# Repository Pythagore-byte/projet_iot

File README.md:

# projet_iot

## Project Overview

This repository contains an IoT project involving sensor data collection, backend processing, and a frontend dashboard. It encompasses Arduino firmware for sensor interfacing, a Python-based backend for data management and MQTT communication, a KiCad design for custom hardware, and a TypeScript/Next.js frontend for data visualization and user interaction.

## Key Features & Benefits

- **Multi-Sensor Integration:** Supports various sensors including temperature, humidity, soil moisture, CO2, and light.
- **LoRaWAN Connectivity:** Utilizes LoRaWAN for long-range, low-power data transmission.
- **Data Processing & Storage:** Employs a Python backend with SQLite database for data ingestion, processing, and storage.
- **Real-time Data Visualization:** Provides a user-friendly dashboard built with Next.js to monitor sensor data in real-time.
- **Custom Hardware Design:** Includes KiCad files for building custom PCB hardware.
- **Containerized Deployment:** Docker support for backend and frontend simplifies deployment and ensures consistency.

## Prerequisites & Dependencies

Before you begin, ensure you have the following installed:

- **Arduino IDE:** For flashing the Arduino firmware.
- **Python 3.11:** For running the backend server and related scripts.
- **Node.js and npm:** For building and running the frontend application.
- **Docker and Docker Compose:** For containerized deployment.
- **KiCad:** For viewing and editing the hardware design files.

**Specific Python Dependencies (Backend):**

- `fastapi`
- `uvicorn`
- `paho-mqtt`
- `sqlite3`
- `python-dotenv`

Install them using:

```bash
pip install -r backend/requirements.txt
```

**Specific Node.js Dependencies (Frontend):**

Refer to `frontend/package.json` for a complete list.  Install them using:

```bash
cd frontend
npm install
```

## Installation & Setup Instructions

Follow these steps to set up and run the project:

1. **Clone the Repository:**

   ```bash
   git clone https://github.com/Pythagore-byte/projet_iot.git
   cd projet_iot
   ```

2. **Arduino Firmware (Arduino_TTN):**

   - Open `Arduino_TTN/Arduino_TTN.ino` in the Arduino IDE.
   - Configure the necessary libraries and board settings for your specific hardware.
   - Modify the LoRaWAN credentials and sensor configurations as needed.
   - Upload the firmware to your Arduino device.

3. **Backend Setup:**

   - Navigate to the `backend` directory:

     ```bash
     cd backend
     ```

   -  Set up environment variables if needed (e.g., for production). Consider using `.env` file and `python-dotenv`.

   -  Initialize the database (if not already present):
      - Development Database:
        ```bash
        python dev_db_generator.py
        ```
      - Production Database:
        ```bash
        python prod_db_generator.py
        ```
      - Or use the provided `db.db` file.

   - Run the backend server:

     ```bash
     python server.py
     ```

     Alternatively, for Docker deployment, see step 5.

4. **Frontend Setup:**

   - Navigate to the `frontend` directory:

     ```bash
     cd ../frontend
     ```

   - Install the dependencies:

     ```bash
     npm install
     ```

   - Configure API endpoint in `frontend/lib/api.ts` to point to your backend server.

   - Run the development server:

     ```bash
     npm run dev
     ```

     This will start the frontend application, typically on `http://localhost:3000`.

5. **Docker Compose Deployment:**

   - From the project root directory, run:

     ```bash
     docker-compose up --build
     ```

   - This will build and start both the backend and frontend containers. Access the frontend through the port defined in the `docker-compose.yml` file (usually `http://localhost:3000`).

6. **KiCad Files (KICAD_FILES):**

   - Open the `.kicad_pcb` and `.kicad_sch` files in KiCad to view and modify the hardware design.

## Usage Examples & API Documentation

### Backend API (Example):

The backend provides a REST API for accessing sensor data.  Example endpoints:

- `GET /data`: Returns all sensor data.
- `GET /data/{device_id}`: Returns data for a specific device ID.

Refer to `backend/server.py` for detailed API route definitions.

### Frontend Usage:

The frontend provides a user interface for visualizing sensor data. Navigate to the appropriate page in your browser to see the collected data and related analysis. The routes `/soil-data`, `/temperature-humidity` and `/plant-suitability` will show the corresponding information.

## Configuration Options

### Backend Configuration:

- **Database Path:** The path to the SQLite database can be configured in `backend/server.py`.
- **MQTT Configuration:** The MQTT broker address, port, app ID, device ID and access key can be configured in `backend/mqtt_adder.py`.
- **Port:** The backend server port can be configured via the `--port` flag when starting the server (e.g., `uvicorn server:app --host 0.0.0.0 --port 8000`).

### Frontend Configuration:

- **API Endpoint:** The backend API endpoint URL should be defined in `frontend/lib/api.ts`.
- **Environment Variables:** Use environment variables in `next.config.js` to configure aspects of frontend deployment.

## Contributing Guidelines

We welcome contributions to this project! To contribute:

1. Fork the repository.
2. Create a new branch for your feature or bug fix.
3. Implement your changes.
4. Submit a pull request with a clear description of your changes.
5. Ensure code follows style conventions and has proper documentation.

## License Information

This project has no specific license specified. All rights are reserved by the owner.

## Acknowledgments

- This project utilizes open-source libraries and tools. We thank the developers and maintainers of these resources.

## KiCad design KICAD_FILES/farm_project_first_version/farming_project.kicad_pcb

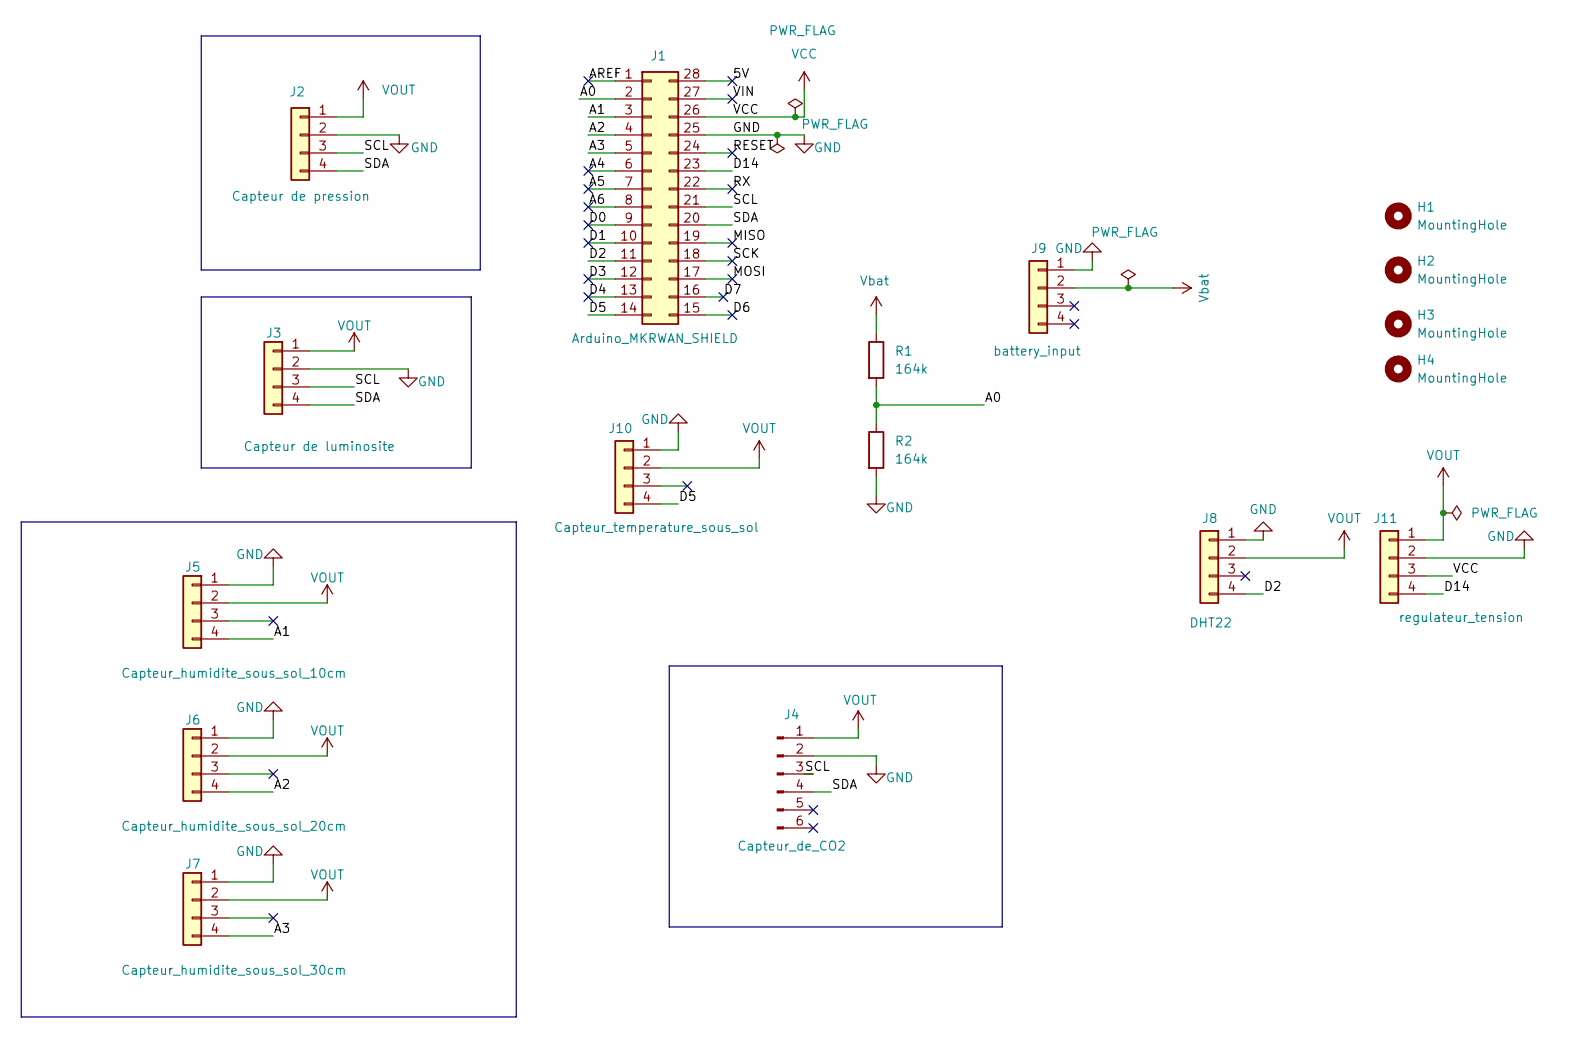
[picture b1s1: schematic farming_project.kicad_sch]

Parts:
H1, H2, H3, H4: MountingHole; MountingHole_2.5mm_Pad
J1: Arduino_MKRWAN_SHIELD; BOARD_ARDUINO_MKR_WAN_1310_MODIFIED
J2: Capteur de pression; PinSocket_1x04_P2.54mm_Vertical
J3: Capteur de luminosite; PinHeader_1x04_P2.54mm_Vertical
J4: Capteur_de_CO2; PinSocket_1x06_P2.54mm_Vertical
J5: Capteur_humidite_sous_sol_10cm; JST_PH_B4B-PH-K_1x04_P2.00mm_Vertical
J6: Capteur_humidite_sous_sol_20cm; JST_PH_B4B-PH-K_1x04_P2.00mm_Vertical
J7: Capteur_humidite_sous_sol_30cm; JST_PH_B4B-PH-K_1x04_P2.00mm_Vertical
J8: DHT22; JST_PH_B4B-PH-K_1x04_P2.00mm_Vertical
J9: battery_input; JST_PH_B4B-PH-K_1x04_P2.00mm_Vertical
J10: Capteur_temperature_sous_sol; JST_PH_B4B-PH-K_1x04_P2.00mm_Vertical
J11: regulateur_tension; PinHeader_1x04_P2.54mm_Vertical
R1, R2: 164k; R_Axial_DIN0309_L9.0mm_D3.2mm_P12.70mm_Horizontal

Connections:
/5V: J1.28
/A0: J1.2, R1.2, R2.1
/A1: J1.3, J5.4
/A2: J1.4, J6.4
/A3: J1.5, J7.4
/A4: J1.6
/A5: J1.7
/A6: J1.8
/AREF: J1.1
/D0: J1.9
/D1: J1.10
/D2: J1.11, J8.4
/D3: J1.12
/D4: J1.13
/D5: J1.14, J10.4
/D6: J1.15
/D7: J1.16
/D14: J1.23, J11.4
/MISO: J1.19
/MOSI: J1.17
/RESET: J1.24
/RX: J1.22
/SCK: J1.18
/SCL: J1.21, J2.3, J3.3, J4.3
/SDA: J1.20, J2.4, J3.4, J4.4
/VIN: J1.27
GND: J1.25, J2.2, J3.2, J4.2, J5.1, J6.1, J7.1, J8.1, J9.1, J10.1, J11.2, R2.2
VCC: J1.26, J11.3
VOUT: J2.1, J3.1, J4.1, J5.2, J6.2, J7.2, J8.2, J10.2, J11.1
Vbat: J9.2, R1.1

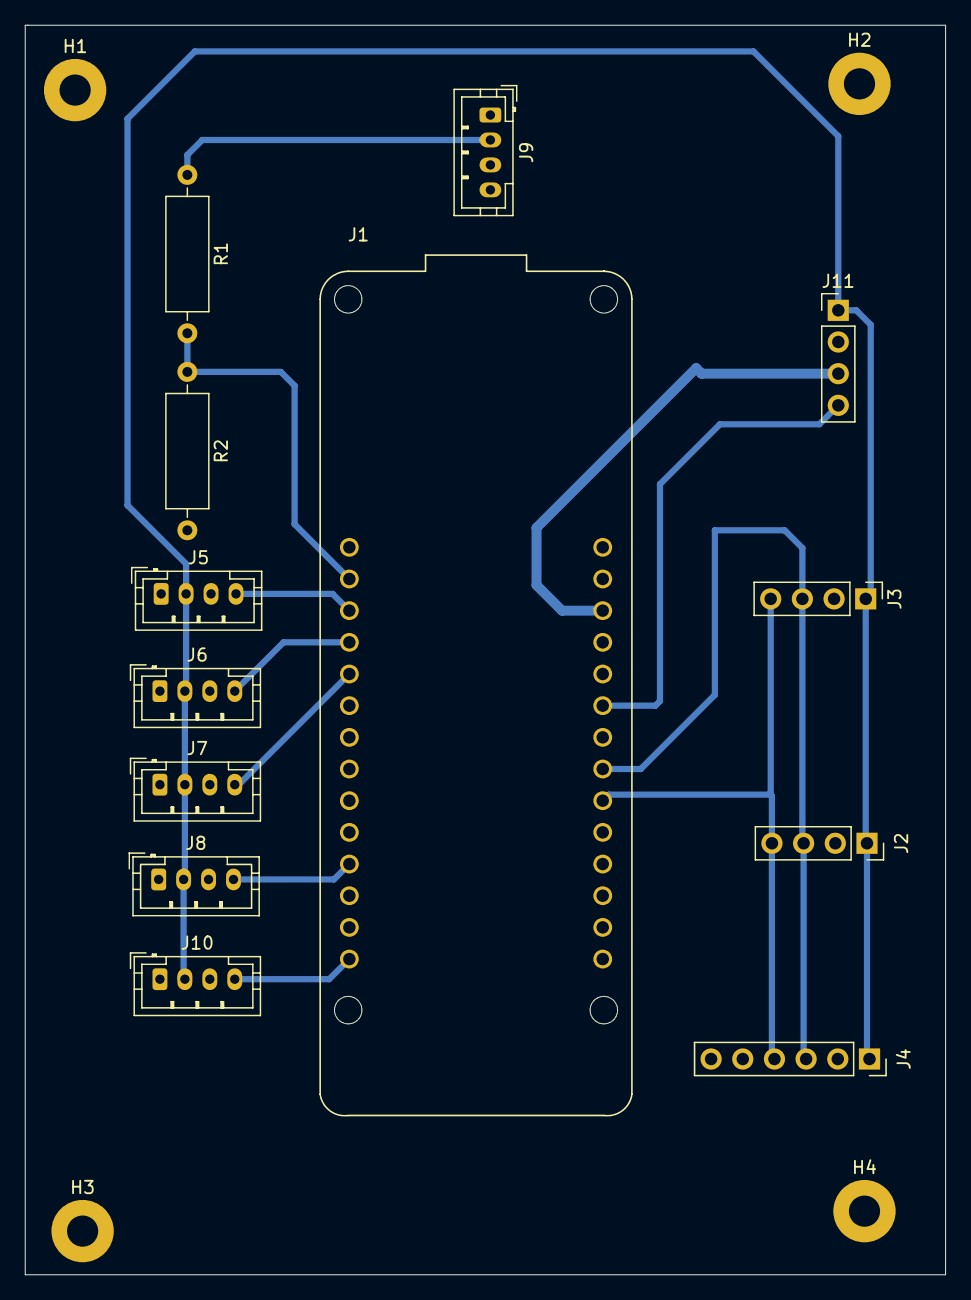
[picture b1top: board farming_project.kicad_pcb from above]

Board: 2 copper layers, 73.8 x 100.2 mm, 17 parts (0 on the bottom side), 13 nets.

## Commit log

2025-02-14 Frontend files upload
2025-02-18 Implement initial backend and frontend structure with database setup and UI components
2025-02-18 Push
2025-02-18 Refactor backend database structure and update frontend dependencies
2025-02-18 color update
2025-02-23 soil page implementation
2025-02-23 Enhance root system visualization with fractal-like pattern and adjust line thickness
2025-02-23 Update tick formatter to display date and time in soil moisture page
2025-02-24 added responsivness
2025-02-24 Add recorded_at timestamp to Errors table and update error retrieval in API
2025-02-26 Sauvegarde des modifications avant checkout
2025-02-26 Receiver.py pour la connexion MQTT
2025-02-26 Refactor database schema by removing Type table and updating Device table constraints; enhance data insertion methods and API queries for improved measurement retrieval.
2025-02-26 updated db schema
2025-03-11 added co2, pressure, luminosity and battery levels
2025-03-11 implemented the header
2025-03-12 added docker files. modified db population and made the first version of the dashboard
2025-03-12 Lora
2025-03-12 Code Capteur
2025-03-12 Adder
2025-03-13 first version of pcb
2025-03-15 deuxieme version PCB
2025-03-17 Rename Mqtt_adder.py to mqtt_adder.py
2025-03-20 mise a jour des code
2025-04-01 Add sensor value validation and timezone conversion for error timestamps
2025-04-02 db update
2025-04-02 Code avec pression bien
2025-04-06 Enhance error handling and add graph maximization feature in temperature and humidity page
2025-04-07 Réparation lundi 07/04
2025-04-07 Update README.md with project overview, features, setup instructions, and contribution guidelines
2025-07-29 mise a jour
